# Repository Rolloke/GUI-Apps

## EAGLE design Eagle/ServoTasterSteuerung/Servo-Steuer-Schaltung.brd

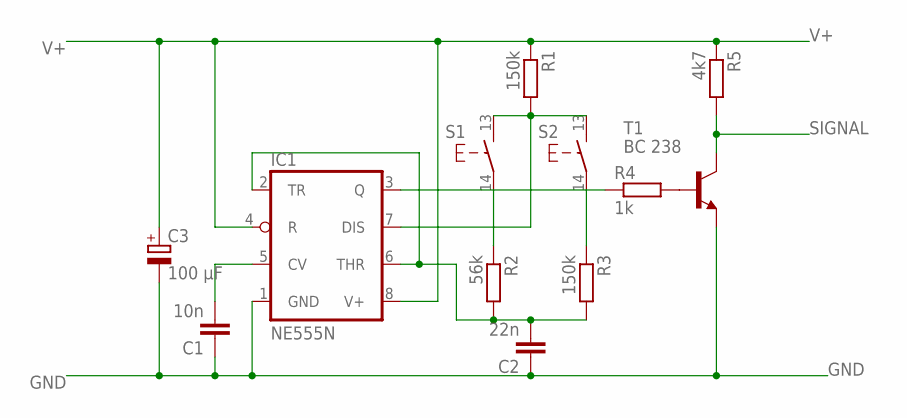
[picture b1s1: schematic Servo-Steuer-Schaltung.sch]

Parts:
C1: 10n; C10B4
C2: 22n; C10B4
C3: 100 µF; E2,5-7
IC1: NE555N; DIL08
R1, R3: 150k; 0207/10
R2: 56k; 0207/10
R4: 1k; 0207/10
R5: 4k7; 0207/10
S1, S2: TASTER_SCHLIESSER; EINTASTER
T1: BC 238; TO92-CBE

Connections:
GND: C1.1, C2.1, C3.-, IC1.1 (GND), T1.E
unnamed: IC1.3 (Q), R4.1
unnamed: R2.1, S1.14
unnamed: R3.1, S2.14
unnamed: C2.2, IC1.2 (TR), IC1.6 (THR), R2.2, R3.2
unnamed: IC1.7 (DIS), R1.2, S1.13, S2.13
unnamed: R4.2, T1.B
unnamed: C1.2, IC1.5 (CV)
SIGNAL: R5.2, T1.C
V+: C3.+, IC1.4 (R), IC1.8 (V+), R1.1, R5.1

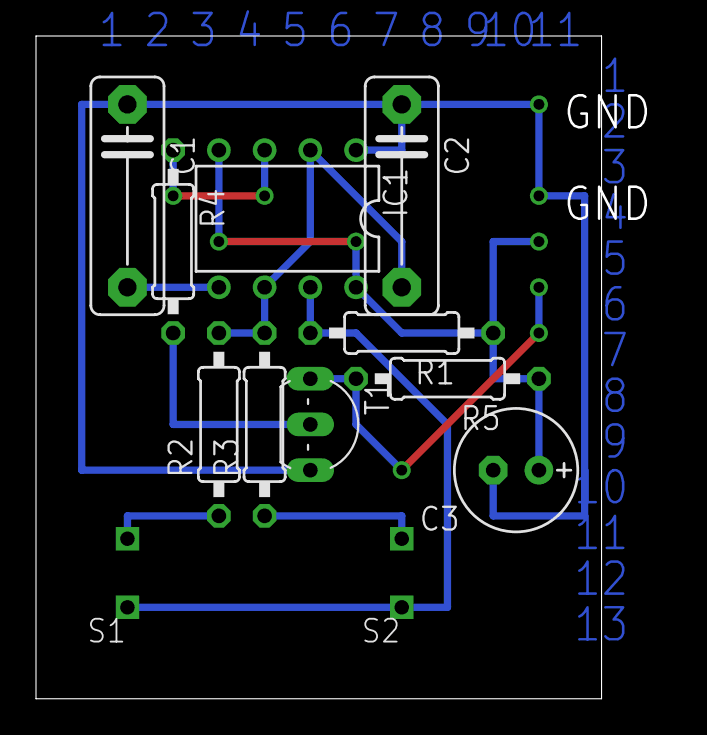
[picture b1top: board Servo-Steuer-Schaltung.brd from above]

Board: 2 copper layers, 31.4 x 36.8 mm, 12 parts (0 on the bottom side), 10 nets.

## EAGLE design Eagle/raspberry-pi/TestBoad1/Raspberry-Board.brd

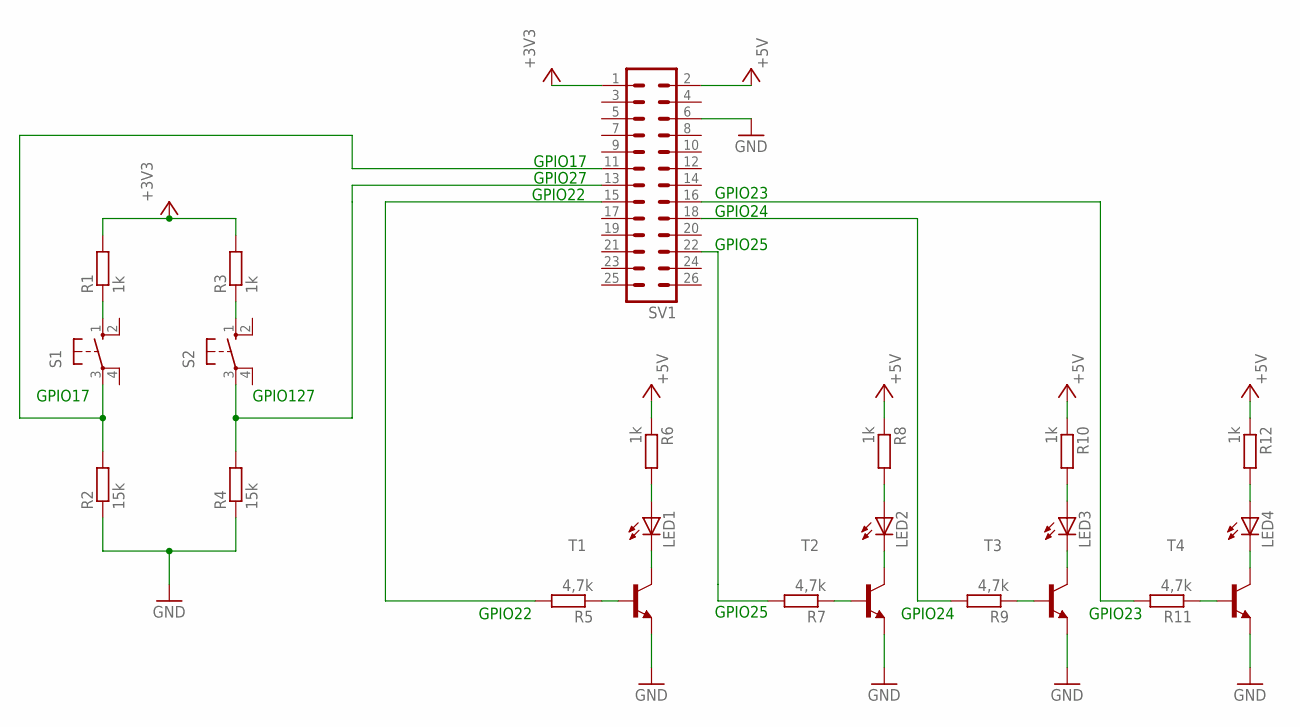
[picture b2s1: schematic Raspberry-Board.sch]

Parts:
LED1, LED2, LED3, LED4: LEDCHIPLED_1206; CHIPLED_1206
R1, R3, R6, R8, R10, R12: 1k; R0805
R2, R4: 15k; R0805
R5, R7, R9, R11: 4,7k; R0805
S1, S2: 10-XX; B3F-10XX
SV1: MA13-2
T1, T2, T3, T4: BC817-16-NPN-SOT23-BEC; SOT23-BEC

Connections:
+3V3: R1.2, R3.2, SV1.1
+5V: R6.1, R8.1, R10.1, R12.1, SV1.2
GND: R2.1, R4.1, SV1.6, T1.E, T2.E, T3.E, T4.E
unnamed: R1.1, S1.1 (S)
unnamed: R3.1, S2.1 (S)
unnamed: R2.2, S1.3, SV1.11
unnamed: R4.2, S2.3, SV1.13
unnamed: LED1.A, R6.2
unnamed: LED1.C, T1.C
unnamed: R5.1, T1.B
unnamed: R5.2, SV1.15
unnamed: LED2.A, R8.2
unnamed: LED2.C, T2.C
unnamed: R7.1, T2.B
unnamed: LED3.A, R10.2
unnamed: LED3.C, T3.C
unnamed: R9.1, T3.B
unnamed: R7.2, SV1.22
unnamed: LED4.A, R12.2
unnamed: LED4.C, T4.C
unnamed: R11.1, T4.B
unnamed: R9.2, SV1.18
unnamed: R11.2, SV1.16

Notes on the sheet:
GPIO17
GPIO127
GPIO22
GPIO25
GPIO24
GPIO23
GPIO27

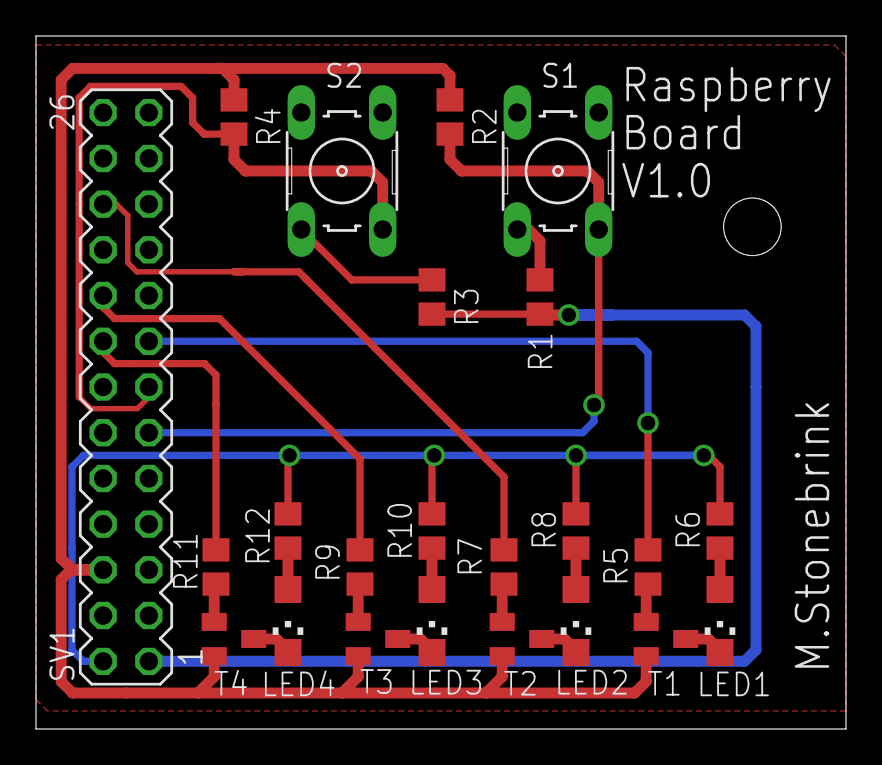
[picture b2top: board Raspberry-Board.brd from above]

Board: 2 copper layers, 45.0 x 38.5 mm, 23 parts (0 on the bottom side), 23 nets.
